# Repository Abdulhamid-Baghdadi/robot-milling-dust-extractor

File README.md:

# MMR3 – Autonomous Dust Extractor for a Robot Milling Station

A motorised, collision-aware dust and chip extractor for robot machining cells. The suction inlet sits on a linear actuator and moves along the spindle axis: the robot controller sets the inlet position with an analog signal that matches the length of the tool in use, and a load-cell collision protector makes the inlet stop or retract when it hits something.
Built for the KUKA KR 16 milling station in the Digital Factory at UAS Technikum Wien, as a solo master's project (Mechatronics/Robotics, 3rd semester, 2021/22).

<sub>Left: 1 exhaust tube inlet, 2 flexible brush, 3 non-captive linear actuator, 4 collision protector, 5 load cell, 6 electronics lid. Right: the printed prototype.</sub>

<sub>Left: air flows from the brush-lined inlet to the hose connector. Right: the collision shield (1) mounted on two load cells (2).</sub>

---

## The problem

A robot arm can mill large or oddly shaped parts without a machine table, but the dust goes everywhere. A fixed hose has to stay far from the tool so the robot does not hit it, which means high suction power and big chips are left behind. A hood or enclosure costs even more energy. Bringing the inlet close to the cutter requires it to:

- stay out of the way of the **automatic tool changer** (only ~44 mm of clearance at the collet),
- adapt to **tools of different lengths**,
- avoid **collisions** with the workpiece and fixtures that the robot program does not know about,
- be controllable **from the robot program** itself.

## Highlights

- **Variable-length inlet:** a Nanotec non-captive stepper linear actuator (lead screw through the rotor) moves the inlet on four linear shafts. It holds its position without a brake when powered off.
- **Set point from the robot:** the KUKA KR C4 sets the inlet position with an analog output (BNC input). The ESP32 maps it to 5 000 – 28 000 steps.
- **Collision protector:** a shield mounted on two strain-gauge load cells (HX711 amplifiers). An Arduino Nano classifies the force into *none / light / hard* and signals the ESP32. On light contact the inlet holds its position. On hard contact it retracts 4 000 steps.
- **Automatic homing** on start-up with an end-stop sensor.
- **Fully 3D-printed body** (PLA, ~900 g) with threaded inserts. About €200 in materials.

## System architecture

```mermaid
flowchart LR
    KRC["KUKA KR C4<br/>robot controller"]
    ESP["ESP32 (NodeMCU)<br/>motor controller"]
    NANO["Arduino Nano<br/>weight reader"]
    HX["2× HX711 +<br/>load cells"]
    DRV["Stepper driver"]
    MOT["Non-captive<br/>linear actuator"]
    HOME["Homing sensor"]

    KRC -- "analog set point<br/>(BNC)" --> ESP
    HX -- "raw force" --> NANO
    NANO -- "BIG_WEIGHT /<br/>SMALL_WEIGHT (digital)" --> ESP
    HOME --> ESP
    ESP -- "STEP / DIR / EN" --> DRV --> MOT
```

### Control loop (ESP32)

```mermaid
flowchart TD
    A[Power on] --> B[Home: drive until homing sensor triggers, set position 0]
    B --> C[Read analog set point, ignore changes under 200 counts]
    C --> D{Collision signal?}
    D -- "hard" --> E[Retract 4000 steps]
    D -- "light" --> F[Hold position]
    D -- "none" --> G[Drive towards set point]
    E --> C
    F --> C
    G --> C
```

## Hardware

### Electronics

Two perfboards connected by pin headers: board 1 holds the ESP32 DevKit V1 (stepper control, BNC set-point input, 12 V DC jack, homing sensor). Board 2 holds the Arduino Nano and two HX711 load-cell amplifiers.

| Signal | ESP32 pin | Notes |
|---|---|---|
| MOTOR_STEP / DIR / ENABLE | GPIO 4 / 2 / 15 | to stepper driver |
| Analog set point | GPIO 34 (ADC) | from KR C4 via BNC |
| BIG_WEIGHT / SMALL_WEIGHT | GPIO 21 / 19 | from Nano D12 / D11 |
| Homing sensor | GPIO 26 in firmware | the schematic routes it to IO14. Check your wiring. |

Eagle sources and a PDF export are in [`hardware/`](hardware).

## Firmware

| Sketch | Board | Role |
|---|---|---|
| [`firmware/motor_controller_esp32`](firmware/motor_controller_esp32) | ESP32 | homing, set-point tracking, collision reaction (AccelStepper) |
| [`firmware/weight_reader_nano`](firmware/weight_reader_nano) | Arduino Nano | reads both load cells (HX711, gain 32, 10-sample average), outputs light/hard collision flags |

**Dependencies** (install with the Arduino Library Manager, not vendored here):
- [HX711](https://github.com/bogde/HX711) by Bogdan Necula (MIT)
- [AccelStepper](https://www.airspayce.com/mikem/arduino/AccelStepper/) by Mike McCauley

**Tuning:**
- Collision thresholds in `weight_reader_nano.ino`: `SMALL_WEIGHT_THRESHOLD` / `BIG_WEIGHT_THRESHOLD` (raw HX711 counts, 40 000 / 100 000 in the final firmware). Higher values make the inlet tolerate more pressure before it reacts. Recalibrate if the protector adapter bends.
- Travel range in `motor_controller_esp32.ino`: `map(analogSignal, 0, 4095, 5000, 28000)`.

## Build & run

1. Print the parts in [`cad/`](cad) (SolidWorks parts + assembly; STL files are included for the sensor parts). Mount the rails, actuator and driver with M3 threaded inserts. Press 3 mm strip brushes (or rubber strips) into the inlet channel.
2. Wire the boards following the schematic.
3. Flash `weight_reader_nano` to the Nano and `motor_controller_esp32` to the ESP32.
4. Supply 12 V (max. 1 A) to the DC jack, and connect the robot's analog output to the BNC jack.
5. On power-up the extractor homes, then follows the analog set point.

> ⚠️ ESP32 GPIOs are 3.3 V. Keep the analog set point within 0 – 3.3 V (the original manual says 5 V), and level-shift the Nano's 5 V collision outputs, for example with a voltage divider.

The full assembly and commissioning guide (German) is in [`docs/user-manual-de.pdf`](docs/user-manual-de.pdf).

## Results

From the [project paper](docs/paper-dust-extractor.pdf):
- Mounted on a cartesian CNC milling Styrofoam, the extractor collected **both fine dust and large chips with only a 200 W vacuum cleaner**, because the inlet sits right next to the cutter.
- The two-threshold collision scheme worked: the inlet **stops before its set point when it meets an obstacle** and retracts on a hard hit.
- Lessons learned: the printed moving inlet flexes slightly (the side away from the lead screw lags behind). Stiffer ribs or carbon-fibre filament would fix this. The L-shaped load-cell adapter should be made from metal. The load cells only sense vertical contact, so mounting them at 45° would also catch side hits.
- Next step: validate on the KUKA KR 16 itself (the tests so far used a CNC).

## Repository layout

```
firmware/   ESP32 motor controller + Arduino Nano load-cell reader
hardware/   Eagle schematic/board (Controller-Board-v2) + PDF export
cad/        SolidWorks parts & assembly of the self-designed components, STL for sensor parts
docs/       project paper (EN) and user manual (DE)
media/      GIFs and images used in this README
```

The CAD folder contains only the parts I designed. Purchased components (Nanotec linear actuator, stepper driver, linear bearings and shaft supports, load cell, connectors, push button, screws/inserts) are left out. The assembly will show them as missing references; you can get them from the manufacturers' sites.

## My contribution

Solo project: concept, mechanical design in SolidWorks, 3D printing and assembly, electronics and wiring, firmware for both microcontrollers, testing, the paper, the user manual and the presentation. Supervised by Martin Kainrath at UAS Technikum Wien.

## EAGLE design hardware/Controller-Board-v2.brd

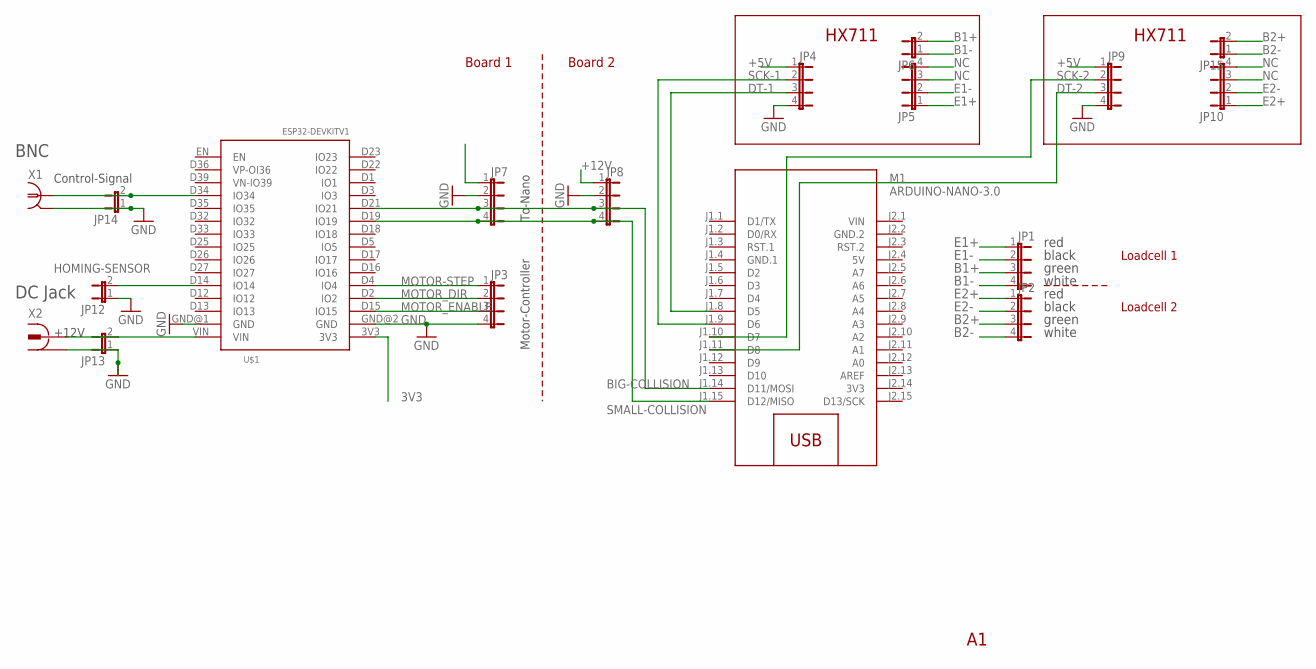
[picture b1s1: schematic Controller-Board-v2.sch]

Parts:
JP1, JP2, JP3, JP4, JP5, JP7, JP8, JP9, JP10: JP4E; JP4
JP6, JP12, JP13, JP14, JP15: JP1E; JP1
M1: ARDUINO-NANO-3.0
U$1: ESP32DEVKITV1; ESP32-DEVKITV1
X1: A1944-50; A1944
X2: 736880-49

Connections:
3V3: M1.J2.14 (3V3), U$1.3V3
5V: M1.J2.4 (5V)
+5V: JP4.1, JP9.1
+12V: JP7.1, JP8.1
B1+: JP1.3, JP6.2
B1-: JP1.4, JP6.1
B2+: JP2.3, JP15.2
B2-: JP2.4, JP15.1
BIG-COLLISION: JP7.3, JP8.3, M1.J1.14 (D11/MOSI), U$1.D21 (IO21)
DT-1: JP4.3, M1.J1.8 (D5)
DT-2: JP9.3, M1.J1.11 (D8)
E1+: JP1.1, JP5.1
E1-: JP1.2, JP5.2
E2+: JP2.1, JP10.1
E2-: JP2.2, JP10.2
GND: JP3.4, JP4.4, JP7.2, JP8.2, JP9.4, JP12.1, JP13.1, JP14.1, U$1.GND@1 (GND), U$1.GND@2 (GND), X1.2, X1.3 (2), X1.4 (2), X1.5 (2), X2.1, X2.1@1 (1), X2.1@2 (1)
GND.1: M1.J1.4 (GND.1)
GND.2: M1.J2.2 (GND.2)
HOMING-SENSOR: JP12.2, U$1.D14 (IO14)
MOTOR-STEP: JP3.1, U$1.D4 (IO4)
MOTOR_DIR: JP3.2, U$1.D2 (IO2)
MOTOR_ENABLE: JP3.3, U$1.D15 (IO15)
unnamed: JP14.2, U$1.D34 (IO34), X1.1
unnamed: JP13.2, U$1.VIN, X2.2
NC: JP5.3, JP5.4, JP10.3, JP10.4
SCK-1: JP4.2, M1.J1.9 (D6)
SCK-2: JP9.2, M1.J1.10 (D7)
SMALL-COLLISION: JP7.4, JP8.4, M1.J1.15 (D12/MISO), U$1.D19 (IO19)
VIN: M1.J2.1 (VIN)

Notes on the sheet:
+12V
Control-Signal
Motor-Controller
To-Nano
HX711
BNC
DC Jack
red
black
green
white
Board 1
Board 2
Loadcell 1
Loadcell 2

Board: 2 copper layers, 18 parts (0 on the bottom side), 25 nets, no tracks yet.

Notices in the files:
parts and their libraries:
diy-modules: Released under the Creative Commons Attribution 4.0 International License: http://creativecommons.org/licenses/by/4.0
